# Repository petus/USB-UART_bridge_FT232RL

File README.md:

# USB-UART_bridge_FT232RL
USB-UART bridge with FT232RL with 3.3V LDO up to 500mA

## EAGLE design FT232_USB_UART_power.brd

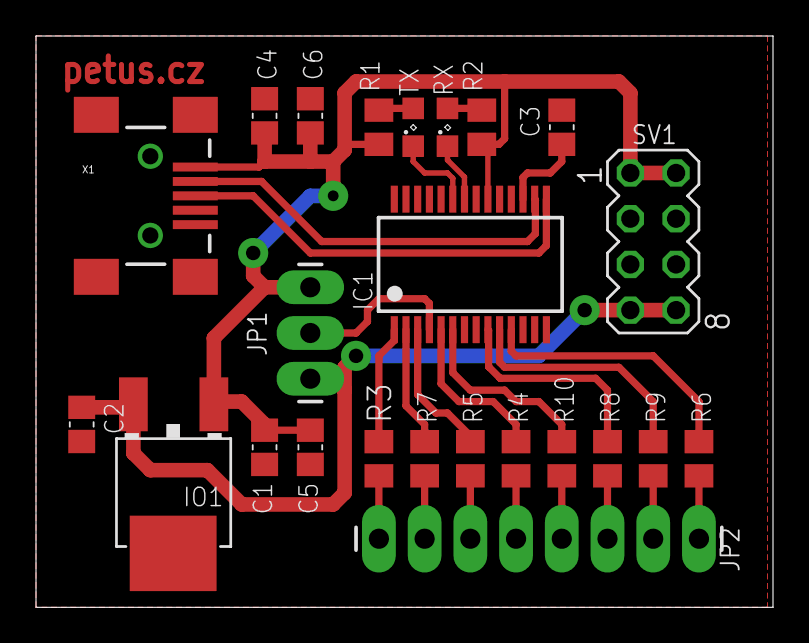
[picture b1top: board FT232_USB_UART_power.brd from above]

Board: 4 copper layers, 40.9 x 31.7 mm, 24 parts (0 on the bottom side), 27 nets.

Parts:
C1, C2, C3, C4, C5, C6: C0805
IC1: FT232RL; SSOP28
IO1: LFDPAK?C; DPAK
JP1: 1X03_LONGPADS
JP2: 1X08_LONGPADS
R1, R2, R3, R4, R5, R6, R7, R8, R9, R10: M0805
RX: SML0805
SV1: MA04-2
TX: SML0805
X1: USB-SMD-NS; USB-MINIB-NOSTOP

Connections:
3V3: C2.1, IO1.3, JP1.1, SV1.7, SV1.8
!CTS: JP2.1, R6.1
!DCD: JP2.2, R9.1
!DSR: JP2.3, R8.1
!DTR: JP2.7, R7.1
!RI: JP2.4, R10.1
!RTS: JP2.6, R5.1
GND: C1.2, C2.2, C3.2, C4.2, C5.2, C6.2, IC1.7, IC1.18, IC1.21, IC1.25, IC1.26, IO1.4, SV1.3, SV1.4, SV1.5, SV1.6, X1.GND
unnamed: IC1.15, X1.D+
unnamed: IC1.16, X1.D-
unnamed: IC1.23, TX.C
unnamed: R1.2, TX.A
unnamed: C3.1, IC1.17
unnamed: IC1.4, JP1.2
unnamed: R2.2, RX.A
unnamed: IC1.22, RX.C
unnamed: IC1.1, R3.2
unnamed: IC1.5, R4.2
unnamed: IC1.3, R5.2
unnamed: IC1.11, R6.2
unnamed: IC1.2, R7.2
unnamed: IC1.9, R8.2
unnamed: IC1.10, R9.2
unnamed: IC1.6, R10.2
RXD: JP2.5, R4.1
TXD: JP2.8, R3.1
VCC: C1.1, C4.1, C5.1, C6.1, IC1.20, IO1.1, JP1.3, R1.1, R2.1, SV1.1, SV1.2, X1.VBUS

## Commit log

2017-05-14 Added pictures fo board and schematic
2017-05-14 Added eagle files of USB-UART bridge with 3.3V LDO

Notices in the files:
parts and their libraries:
Copyright (C) PaJa 2001-2011
SparkFun: Licensing: CC v3.0 Share-Alike You are welcome to use this library for commercial purposes.
